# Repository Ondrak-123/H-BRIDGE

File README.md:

# H BRIDGE

Macondo link: https://macondo.hackclub.com/projects/6541
- The whole step by step explanation and design day by day is on Macondo, I did not want to just copy the whole journals here, here I only included the most important explanations/features so it is nice and organized.

# Quick explanation followed by BOM, schematics and pcb layout :
What is an H Bridge?

H Bridge is a type of circuit that can be used to control speed and rotation of a DC motor, the speed is controlled with PWM (Pulse With Modulation), therefore it can be connected to a microcontroller like Arduino or ESP, if not the direction can be controlled for example by a button. (Essentially, you use the H-bridge to choose the direction (forward/reverse) and the PWM signal to set the speed).
What use does an H Bridge have?

Speed control
Automation
Robotics
What components does an H bridge consists of?

Usually four mosfets (or BJTs in low power and older design, or even IGBTs for high power or industrial applications)
Flyback diodes (motor acts as an inductive load, that can generate voltage spikes, that can kill the mosfets)
Capacitors to filter the noise generated by the motor
Resistors if BJTs are used to limit the base current

- Pictures demonstrating how an H Bridge works:

- (This is the most easiest way to think of an H bridge, we have four switches, by switching on diagonal pair we can change the direction of the motor, and by switching these "switches" ON and OFF we can control the speed (PWM), later the "switches" are replaced by mosfets that are controlled by BJTs.

  **How to solder and use this board:**
- Soldering this board is quite easy, because the SMD componenets are quite large, so no stencil is needed.
- You connect you power source to the input (the one, for the motor), then you control the individual pins (A-H,L / B-H,L), or just simply adding voltage to them, therefore no MCU or firmware is needed. (All the detailed explanation of how this works and why is on the Macondo page).

# BOM: 
- There are two BOMs included, one for EU for a better price and one for the rest of the world.

| Part / Description | Code | Quantity | Price (CZK) | Price (USD) | Link / Notes |
| :--- | :--- | :---: | :---: | :---: | :--- |
| IRFR9024NTRPBF (same alternative) | 915-060 | 2 | 38.00 | - | https://www.gme.cz/v/1493242/infineon-irfr9024ntrpbf-unipolarni-tranzistor |
| IRLR2905PBF (same alternative) | 915-014 | 2 | 66.00 | - | https://www.gme.cz/v/1494225/infineon-irlr2905pbf-unipolarni-tranzistor |
| 100R 0805 | 901-212 | 4 | 20.00 | - | https://www.gme.cz/v/1490056/yageo-r0805-100r-012w-1-smd-rezistor |
| 100nF 50V | 906-096 | 7 | 15.40 | - | https://www.gme.cz/v/1496302/yageo-cks0805-100n-50v-x7r-10-keramicky-kondenzator-smd |
| 10K 0805 | 901-176 | 5 | 20.00 | - | https://www.gme.cz/v/1483919/yageo-r0805-10k-012w-1-smd-rezistor |
| SS34 | 920-028 | 4 | 32.40 | - | https://www.gme.cz/v/1489348/semtech-ss34-smb-schottkyho-dioda |
| BC847 | 912-017 | 11 | 20.90 | - | https://www.gme.cz/v/1489504/semtech-bc847c-bipolarni-tranzistor |
| 1K 0805 | 901-029 | 5 | 15.00 | - | https://www.gme.cz/v/1496399/yageo-r0805-1k-012w-5-smd-rezistor |
| 470uF 25V | 908-032 | 3 | 27.26 | - | https://www.gme.cz/v/1486213/hitano-ces-470u-25vit-hit-ezv-f-10x105-rm1145-elektrolyticky-kondenzator |
| Local Shipping | - | 1 | 69.00 | - | Local GME Shipping |
| **SUBTOTAL (GME.cz)** | - | - | **323.96** | **$15.54** | Exchange Rate: 1 USD = 20.85 CZK |
| **PCB From JLCPCB** | - | 1 | - | **$8.44** | JLCPCB Order |
| **TOTAL** | - | - | - | **$23.98** | Grand Total |
| **Amount Requested** | - | - | - | **$26.00** | Requested Amount |

# Schematics:
- Thanks to explanation both here on GitHub and day by day continual from Macondo, you are now able to create a schematic similar to mine:

# Layout:
- 2 Layer board, the whole board is SMD except the power and data pins, I have used 0805 and DPAK packages.
- Here you can see both front and back layout and 3D rendering:

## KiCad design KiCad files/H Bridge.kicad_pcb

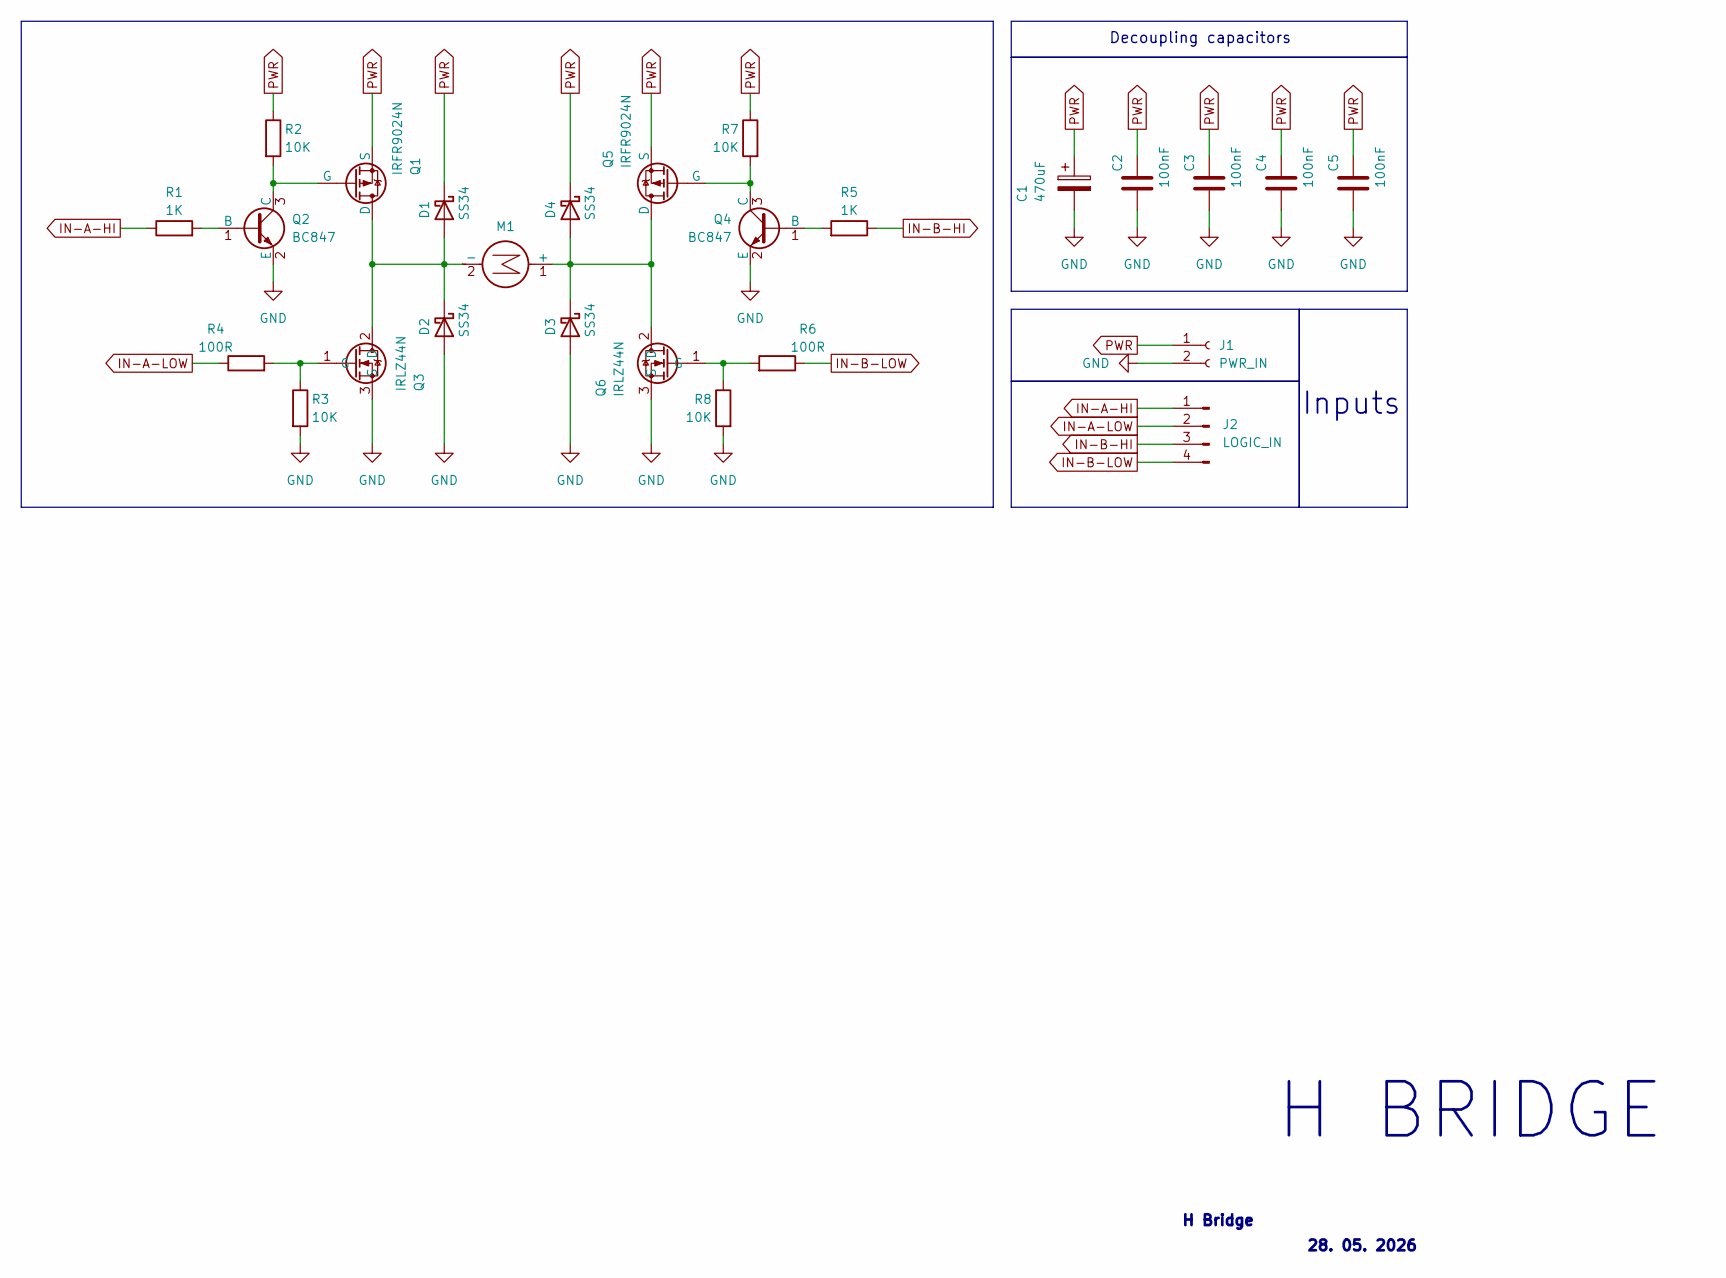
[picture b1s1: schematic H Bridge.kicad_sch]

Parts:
C1: 470uF; CP_Elec_10x10
C2, C3, C4, C5: 100nF; C_0805_2012Metric
D1, D2, D3, D4: SS34; D_SMA
J1: PWR_IN; JST_NV_B02P-NV_1x02_P5.00mm_Vertical
J2: LOGIC_IN; PinHeader_1x04_P2.54mm_Vertical
M1: Motor_DC; JST_NV_B02P-NV_1x02_P5.00mm_Vertical
Q1, Q5: IRFR9024N; TO-252-2
Q2, Q4: BC847; SOT-23
Q3, Q6: IRLZ44N; TO-252-2
R1, R5: 1K; R_0805_2012Metric
R2, R3, R7, R8: 10K; R_0805_2012Metric
R4, R6: 100R; R_0805_2012Metric

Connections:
GND: C1.2, C2.2, C3.2, C4.2, C5.2, D2.2 (A), D3.2 (A), J1.2, Q2.2 (E), Q3.3 (S), Q4.2 (E), Q6.3 (S), R3.2, R8.2
IN-A-HI: J2.1, R1.1
IN-A-LOW: J2.2, R4.1
IN-B-HI: J2.3, R5.1
IN-B-LOW: J2.4, R6.1
unnamed: D1.2 (A), D2.1 (K), M1.2 (-), Q1.1 (D), Q3.2 (D)
unnamed: D3.1 (K), D4.2 (A), M1.1 (+), Q5.1 (D), Q6.2 (D)
unnamed: Q1.2 (G), Q2.3 (C), R2.2
unnamed: Q2.1 (B), R1.2
unnamed: Q3.1 (G), R3.1, R4.2
unnamed: Q4.1 (B), R5.2
unnamed: Q4.3 (C), Q5.2 (G), R7.2
unnamed: Q6.1 (G), R6.2, R8.1
PWR: C1.1, C2.1, C3.1, C4.1, C5.1, D1.1 (K), D4.1 (K), J1.1, Q1.3 (S), Q5.3 (S), R2.1, R7.1

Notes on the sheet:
H BRIDGE
Decoupling capacitors
H Bridge
Inputs
28. 05. 2026

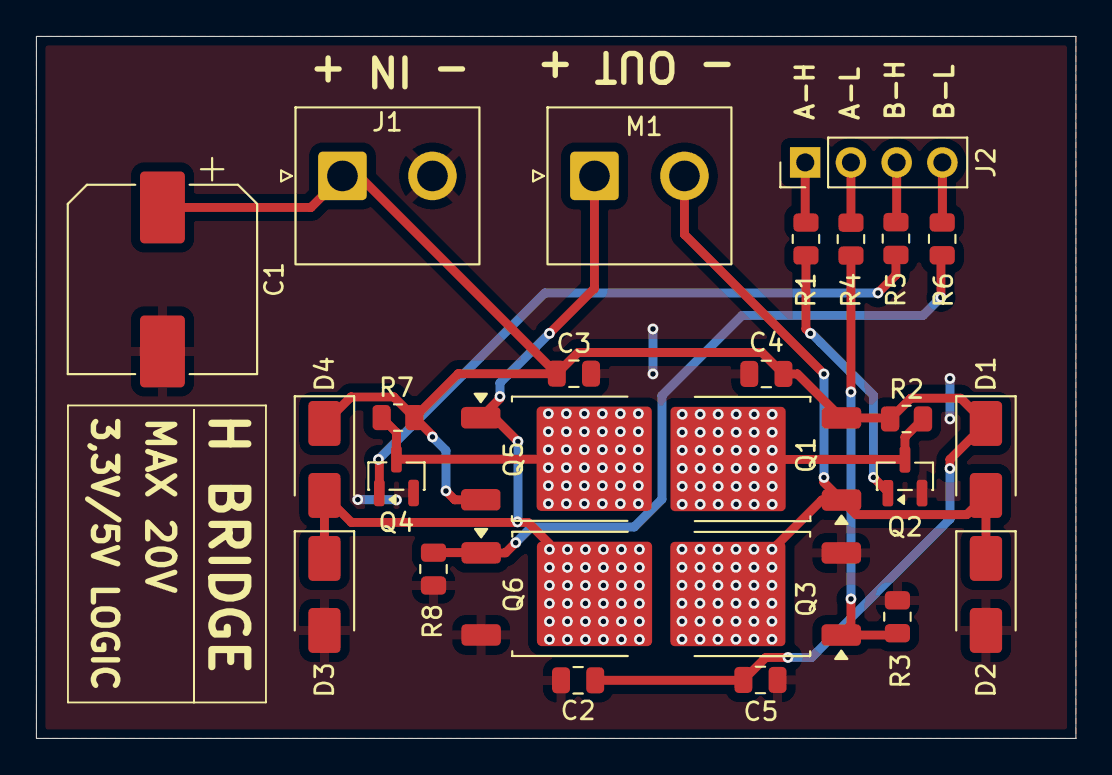
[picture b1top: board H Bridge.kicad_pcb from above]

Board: 2 copper layers, 57.8 x 39.0 mm, 26 parts (0 on the bottom side), 14 nets.

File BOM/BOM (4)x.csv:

;;;;;;;;;;;;;;;;;;;;
;I will use local seller based in the EU to avoid the new tarrif, (https://www.gme.cz/), I also included LCSC breakdown and downloadable cart.;;;;;;;;;;;;The whole LCSC cart can be downloaded on GitHub. (To check all the prices and links).;;;;;;;
;;;;;;;;;;;;;;;;;;;;
;Breakdown from GME.CZ;;;;;;;;;;;;Id;Symbol;Footprint;Quantity;Description;LCSC ID;USD Price;
;Part:;Code:;Ordering quantity (MOQ):;Price (CZK):;;;;;;;;;1;Q6,Q3;TO-252-2;2;IRLZ44N;C2680878;2,11;
;IRFR9024NTRPBF (same alternative);915-060;2;38;;;;;;;;;2;R4,R6;R_0805_2012Metric;2;100R;C2907218;0,23;
;IRLR2905PBF (same alternative);915-014;2;66;;;;;;;;;3;C3,C2,C5,C4;C_0805_2012Metric;4;100nF;C49678;0,65;
;100R 0805;901-212;4;20;;;;;;;;;4;Q5,Q1;TO-252-2;2;IRFR9024N;C41430593;0,45;
;100nF 50V;906-096;7;15,4;;;;;;;;;5;R8,R3,R2,R7;R_0805_2012Metric;4;10K;C2907219;0,22;
;10K 0805;901-176;5;20;;;;;;;;;6;D3,D4,D1,D2;D_SMA;4;SS34;C908680;0,66;
;SS34;920-028;4;32,4;;;;;;;;;7;M1;JST_NV_B02P-NV_1x02_P5.00mm_Vertical;1;Motor_DC;;;
;BC847;912-017;11;20,9;;;;;;;;;8;Q2,Q4;SOT-23;2;BC847;C57668;0,82;
;1K 0805;901-029;5;15;;;;;;;;;9;R5,R1;R_0805_2012Metric;2;1K;C2907232;0,22;
;470uF 25V;908-032;3;27,26;1USD=20,85CZK;;;;;;;;10;C1;CP_Elec_10x10;1;470uF;C72518;0,57;
;Local shipping;;;69;;;;;;;;;11;J1;JST_NV_B02P-NV_1x02_P5.00mm_Vertical;1;PWR_IN;C474881;0,50;
;;;TOTAL IN CZK:;323,96;;15,54USD;;;;;;;12;J2;PinHeader_1x04_P2.54mm_Vertical;1;LOGIC_IN;C52016392;0,62;
;;;;;;+8,44USD;PCB From JLCPCB;;;;;;13;;LCSC Handling fee;1;;;3,00;
;;;;;TOTAL:;23,98USD;;;;;;;14;;LCSC Shipping;1;;;10,20;
;;;;Amount for requesting:;;26USD;;;;;;;15;;JLCPCB PCB;1;PCB;;4,24;
;;;;;;;;;;;;;;;;;;Item Total:;24,49;
;;;;;;;;;;;;;I will not be using this cart/LCSC due to the new high tarrifs for EU, instead I  ;;;;;;;
;;;;;;;;;;;;;will use a seller from my country (GME.CZ), but I also included LCSC so you;;;;;;;
;;;;;;;;;;;;;can purchase and complete this project too.;;;;;;;
;;;;;;;;;;;;;;;;;;;;
;;;;;;;;;;;;;;;;;;;;
;;;;;;;;;;;;;;;;;;;;
;;;;;;;;;;;;;;;;;;;;
;;;;;;;;;;;;;;;;;;;;
;;;;;;;;;;;;;;;;;;;;
;;;;;;;;;;;;;;;;;;;;
;;;;;;;;;;;;;;;;;;;;
;;;;;;;;;;;;;;;;;;;;
;;;;;;;;;;;;;;;;;;;;
;;;;;;;;;;;;;;;;;;;;
;;;;;;;;;;;;;;;;;;;;
;;;;;;;;;;;;;;;;;;;;
;;;;;;;;;;;;;;;;;;;;
;;;;;;;;;;;;;;;;;;;;
;;;;;;;;;;;;;;;;;;;;
;;;;´+ 69CZK shipping;;;;;;;;;;;;;;;;

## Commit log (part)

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2026-06-02 Import
2026-06-02 Readme update
2026-06-20 recommended update
    added another BOM (the same but .xlsx converted to .csv)
